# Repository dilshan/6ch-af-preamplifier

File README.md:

# 5.1 channel audio preamplifier

This project introduces a digitally controlled 5.1 channel audio preamplifier system. This amplifier is specifically designed to increase the gain of the multi-channel PC sound cards.

This preamplifier consists of six *[TL074](https://octopart.com/tl074idt-stmicroelectronics-410591)*/*[TL072](https://octopart.com/tl072idt-stmicroelectronics-410448)* preamplifier stages and *[PT2258](http://www.princeton.com.tw/Portals/0/Product/PT2258.pdf)* electronic volume control. The input stage of this preamplifier consists of six *TL074*/*TL072* buffer stages. The *[PIC16F886](https://www.microchip.com/en-us/product/PIC16F886)* microcontroller manages the *PT2258* electronic volume control IC. All the volume levels and menu options are displayed on [*HD44780*, 16×2 character LCD screen](https://s.click.aliexpress.com/e/_9iRz4T).

The provided PCB design contains a preamplifier, buffer stages, digital volume control circuit, driver circuit, and power supply unit.

The project was sponsored by *[PCBWay](https://www.pcbway.com/setinvite.aspx?inviteid=341430)*. The accurately configured PCB of this preamplifier can directly [order from *PCBWay*](https://www.pcbway.com/project/shareproject/5_1_channel_audio_preamplifier.html) through their website. The dimension of the PCB is 151.45 × 50.76mm.

This preamplifier is a [certified](https://certification.oshwa.org/lk000010.html) open hardware project. All source codes, *KiCAD* design files, and compiled binaries are available at this repository.

The complete [documentation](https://github.com/dilshan/6ch-af-preamplifier/wiki) of this project is available in the [wiki](https://github.com/dilshan/6ch-af-preamplifier/wiki) section of this repository. The PCB *Gerber files* and compiled binaries are also available in the [release](https://github.com/dilshan/6ch-af-preamplifier/releases) section of this repository.

All the content of this project are distributed under the terms of the following license:

- Hardware License: [CERN-OHL-W 2.0](https://ohwr.org/cern_ohl_w_v2.txt)
- Software License: [MIT](https://github.com/dilshan/6ch-af-preamplifier/blob/main/LICENSE)
- [Documentation](https://github.com/dilshan/6ch-af-preamplifier/wiki) License: [CC BY 4.0](https://creativecommons.org/licenses/by/4.0/)

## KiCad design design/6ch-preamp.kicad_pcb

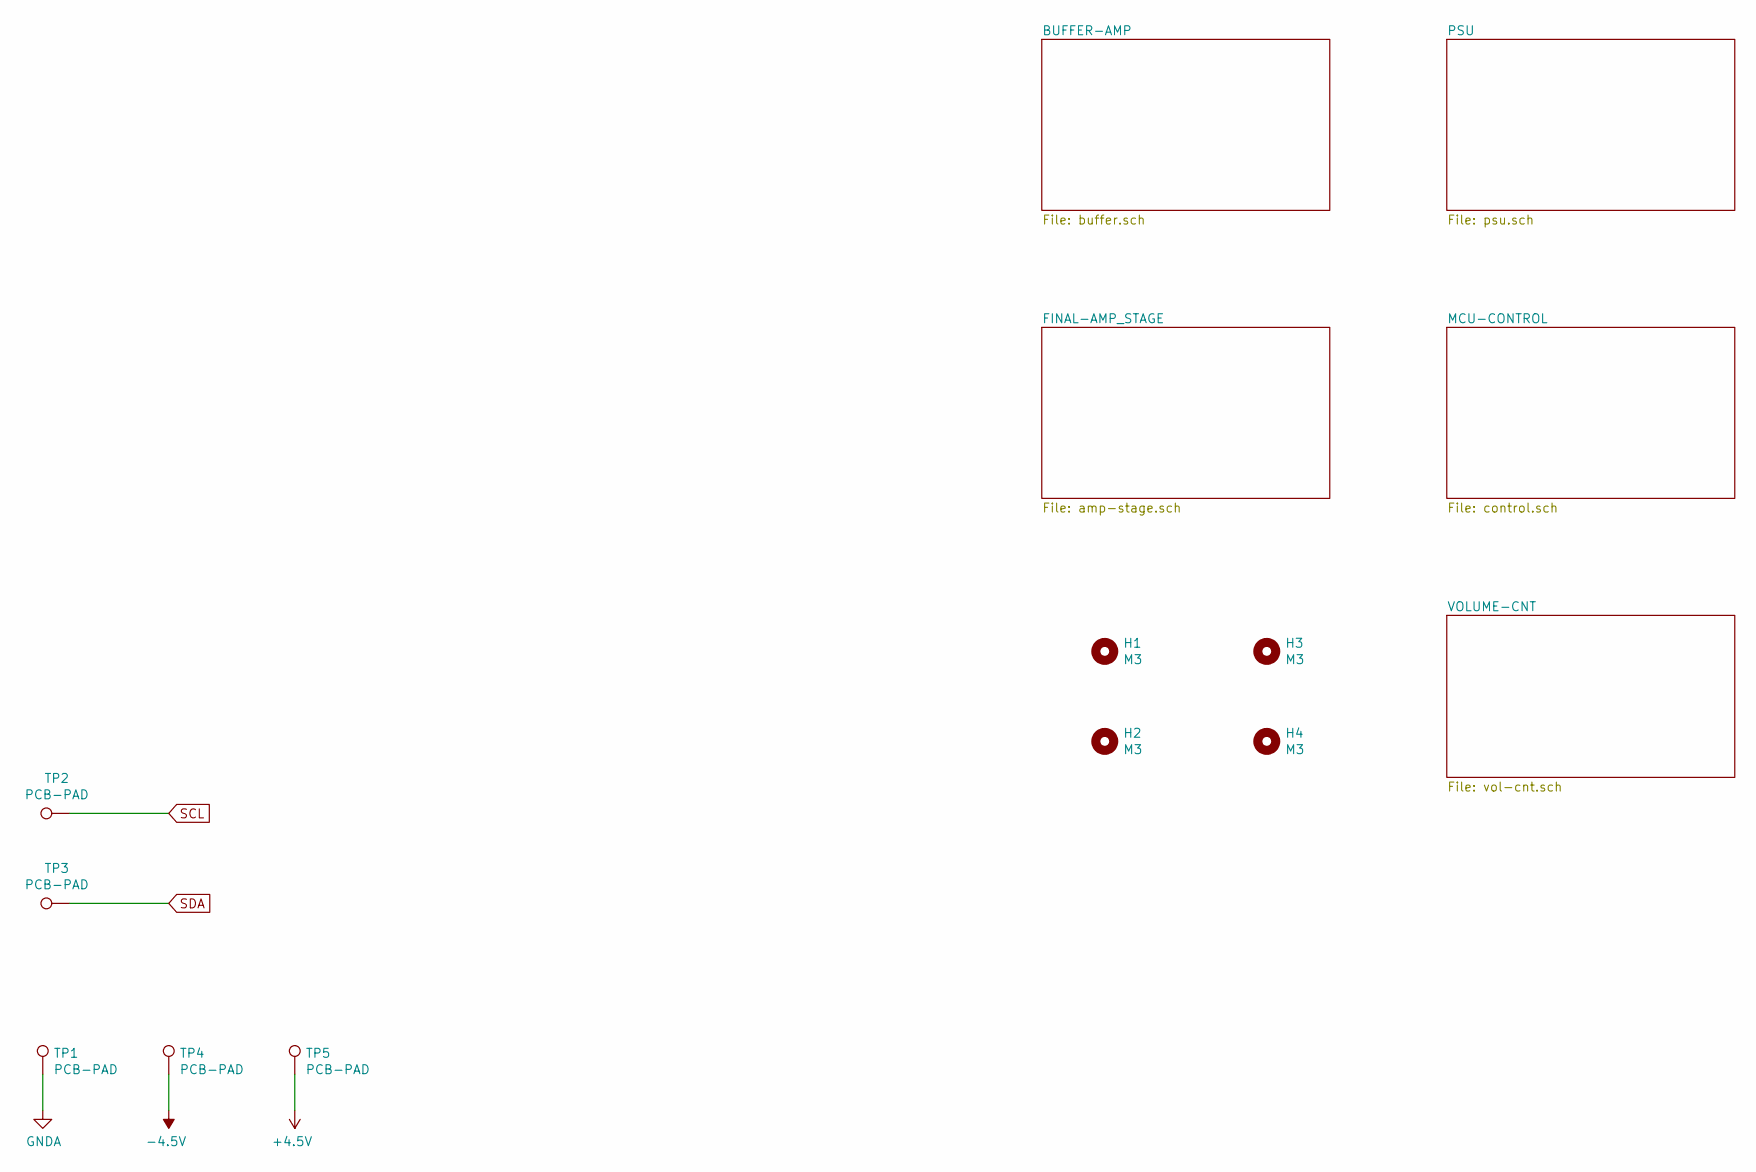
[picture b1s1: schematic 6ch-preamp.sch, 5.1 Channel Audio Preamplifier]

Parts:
H1, H2, H3, H4: M3; MountingHole_3.2mm_M3_DIN965_Pad
TP1, TP2, TP3, TP4, TP5: PCB-PAD; TestPoint_Pad_D2.0mm

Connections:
+1V35: TP5.1; also elsewhere on the board
-5V: TP4.1; also elsewhere on the board
GNDA: TP1.1; also elsewhere on the board
SCL: TP2.1; also elsewhere on the board
SDA: TP3.1; also elsewhere on the board

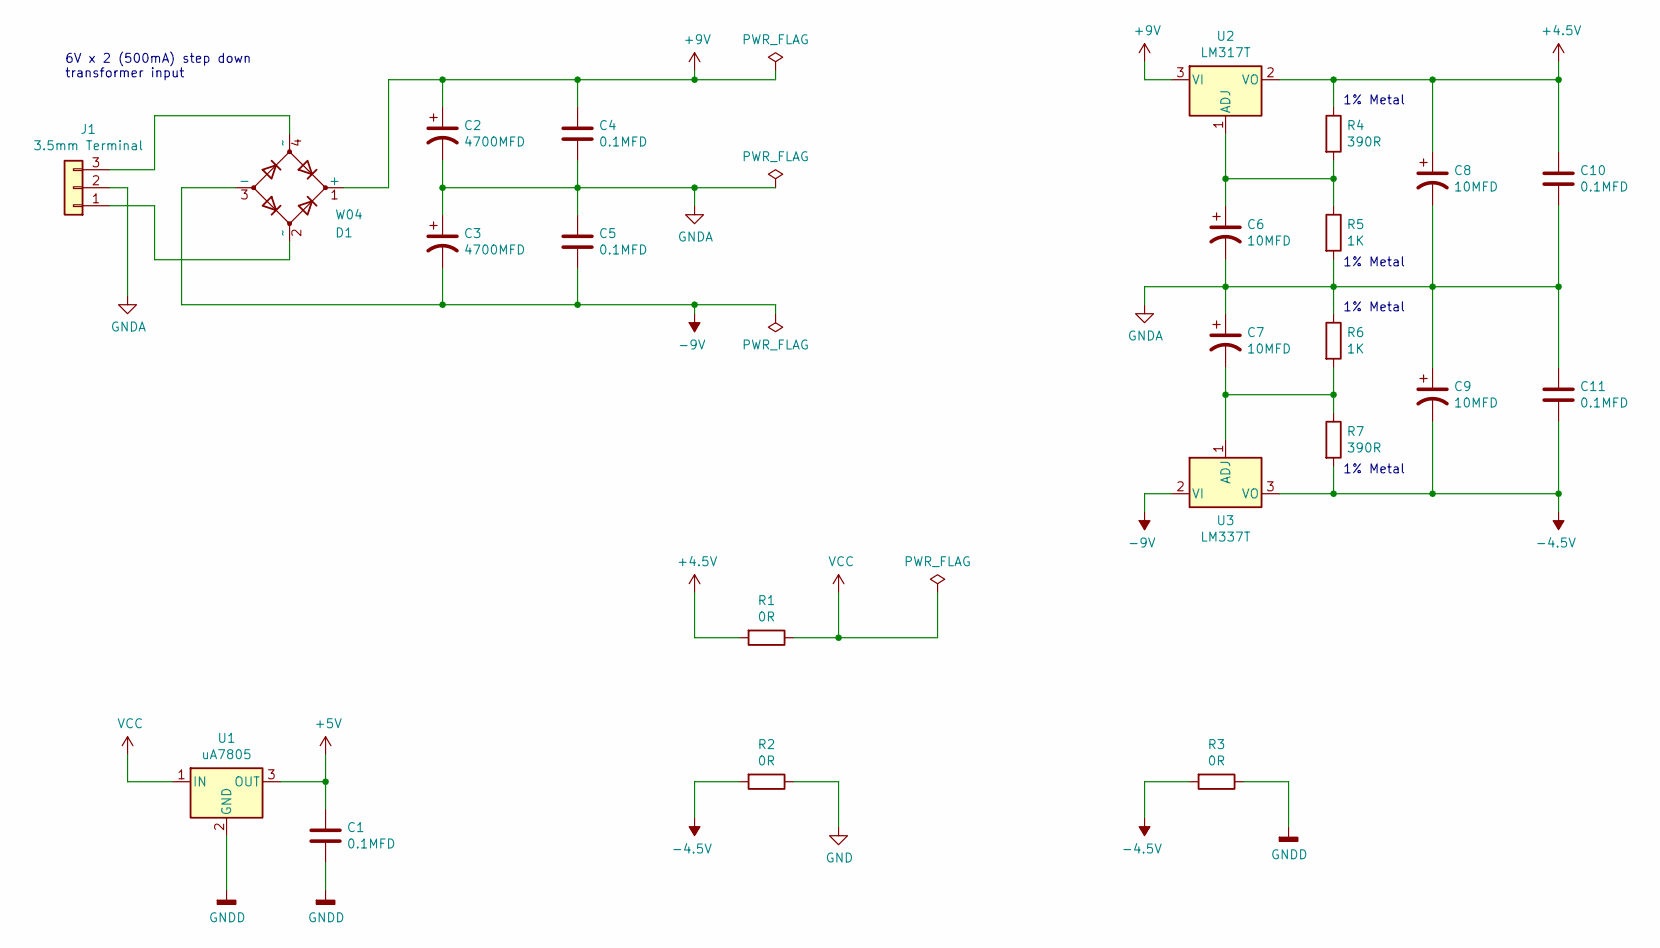
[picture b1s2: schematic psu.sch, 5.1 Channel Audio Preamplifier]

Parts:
C1, C10, C11: 0.1MFD; C_0805_2012Metric_Pad1.18x1.45mm_HandSolder
C2, C3: 4700MFD; CP_Radial_D30.0mm_P10.00mm_SnapIn
C4, C5: 0.1MFD; C_Disc_D10.5mm_W5.0mm_P10.00mm
C6, C7, C8, C9: 10MFD; CP_Elec_5x5.3
D1: W04; Diode_Bridge_Round_D9.0mm
J1: 3.5mm Terminal; PhoenixContact_MCV_1,5_3-G-3.5_1x03_P3.50mm_Vertical
R1, R2, R3: 0R; R_Axial_DIN0204_L3.6mm_D1.6mm_P2.54mm_Vertical
R4, R7: 390R; R_Axial_DIN0207_L6.3mm_D2.5mm_P10.16mm_Horizontal
R5, R6: 1K; R_Axial_DIN0207_L6.3mm_D2.5mm_P10.16mm_Horizontal
U1: uA7805; TO-220-3_Vertical
U2: LM317T; TO-220-3_Vertical
U3: LM337T; TO-220-3_Vertical

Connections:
+1V35: C8.1, C10.1, R1.2, R4.1, U2.2 (VO); also elsewhere on the board
+5V: C1.1, U1.3 (OUT); also elsewhere on the board
+9V: C2.1, C4.1, D1.1 (+), U2.3 (VI)
-5V: C9.2, C11.2, R2.2, R3.2, R7.2, U3.3 (VO); also elsewhere on the board
-9V: C3.2, C5.2, D1.3 (-), U3.2 (VI)
GND: R2.1; also elsewhere on the board
GNDA: C2.2, C3.1, C4.2, C5.1, C6.2, C7.1, C8.2, C9.1, C10.2, C11.1, J1.2, R5.2, R6.1; also elsewhere on the board
GNDD: C1.2, R3.1, U1.2 (GND); also elsewhere on the board
unnamed: C6.1, R4.2, R5.1, U2.1 (ADJ)
unnamed: C7.2, R6.2, R7.1, U3.1 (ADJ)
unnamed: D1.2 (~~), J1.1
unnamed: D1.4 (~~), J1.3
VCC: R1.1, U1.1 (IN); also elsewhere on the board

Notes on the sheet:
6V x 2 (500mA) step down transformer input
1% Metal

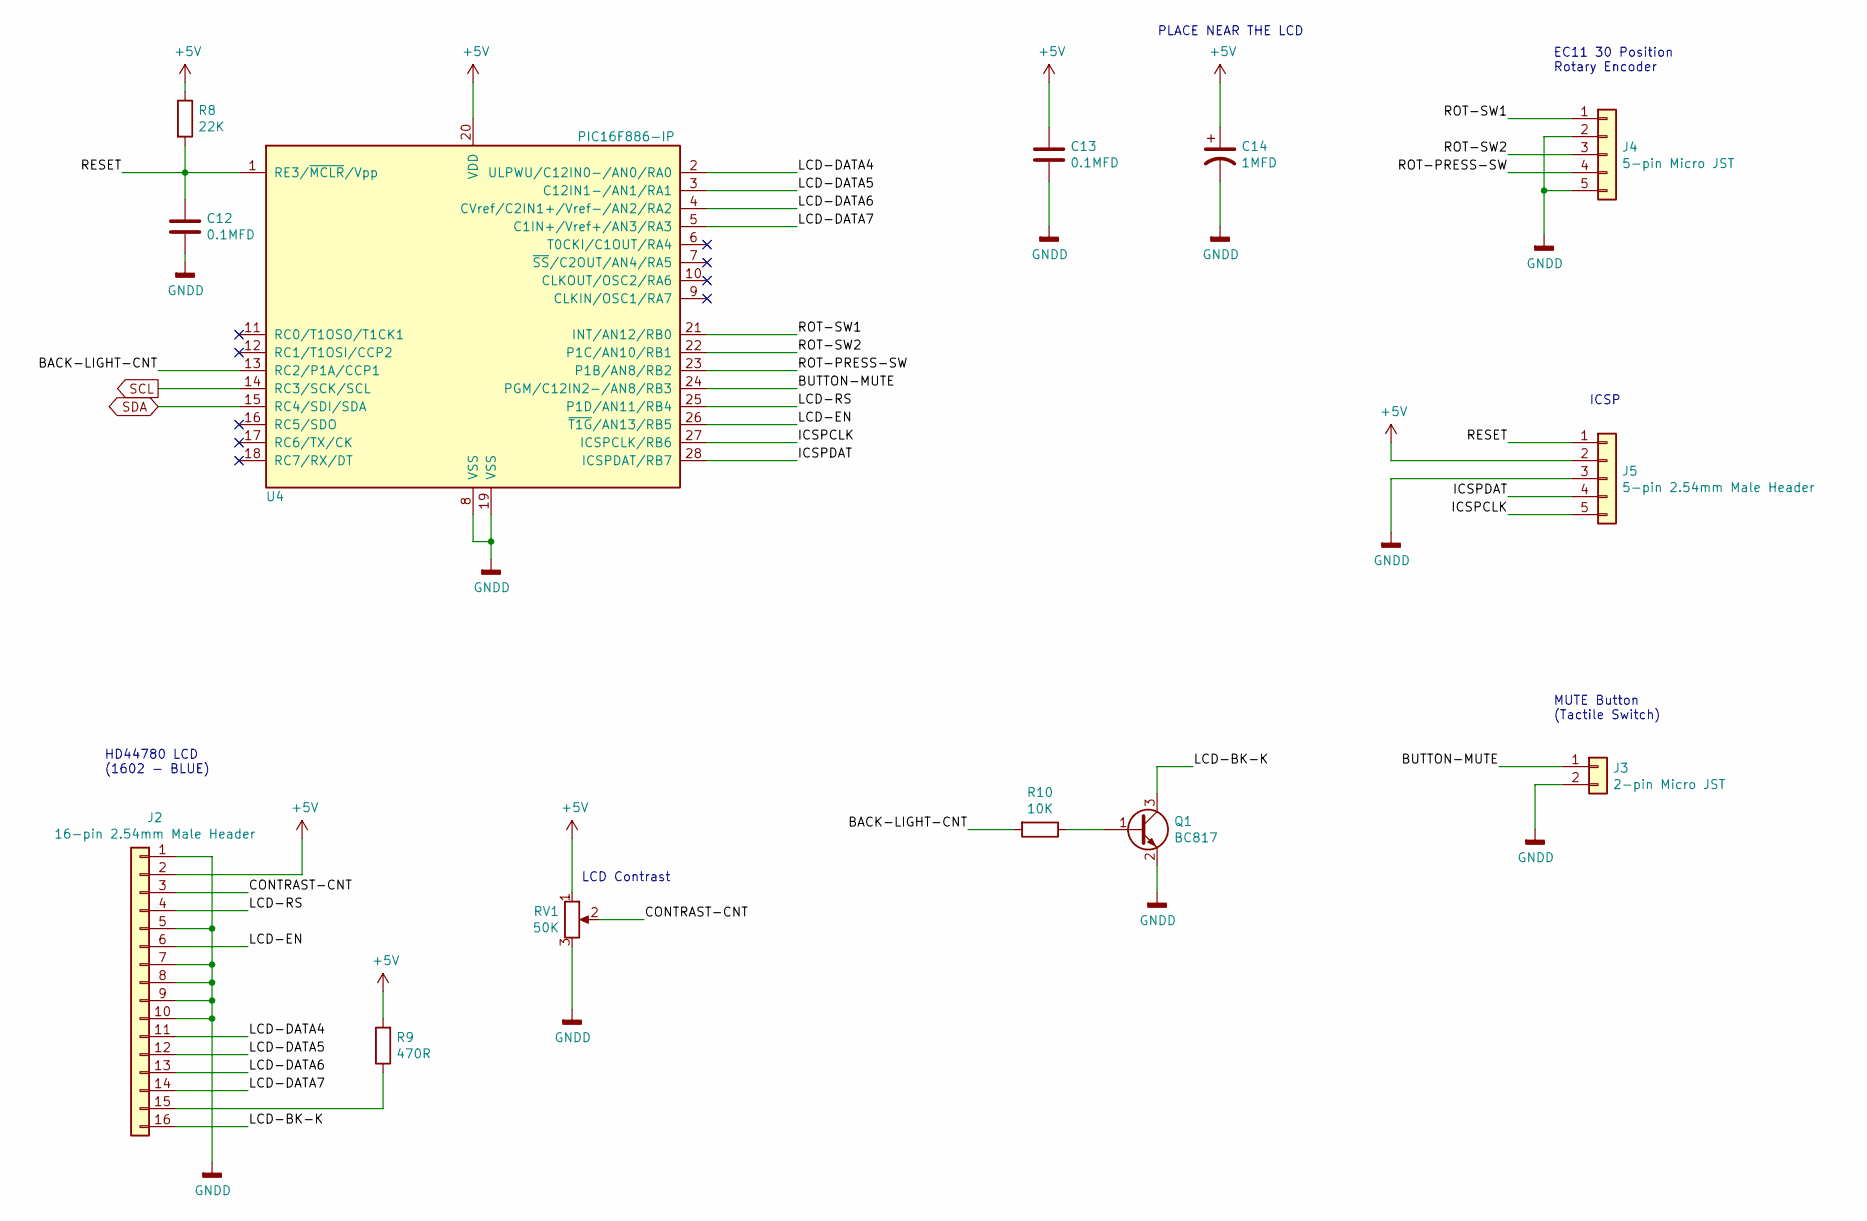
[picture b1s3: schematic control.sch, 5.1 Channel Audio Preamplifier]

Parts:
C12, C13: 0.1MFD; C_0805_2012Metric_Pad1.18x1.45mm_HandSolder
C14: 1MFD; CP_Elec_4x5.3
J2: 16-pin 2.54mm Male Header; PinHeader_1x16_P2.54mm_Vertical
J3: 2-pin Micro JST; JST_EH_B2B-EH-A_1x02_P2.50mm_Vertical
J4: 5-pin Micro JST; JST_EH_B5B-EH-A_1x05_P2.50mm_Vertical
J5: 5-pin 2.54mm Male Header; PinHeader_1x05_P2.54mm_Vertical
Q1: BC817; SOT-23
R8: 22K; R_0805_2012Metric_Pad1.20x1.40mm_HandSolder
R9: 470R; R_0805_2012Metric_Pad1.20x1.40mm_HandSolder
R10: 10K; R_0805_2012Metric_Pad1.20x1.40mm_HandSolder
RV1: 50K; Potentiometer_Bourns_TC33X_Vertical
U4: PIC16F886-IP; SSOP-28_5.3x10.2mm_P0.65mm

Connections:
+5V: C13.1, C14.1, J2.2, J5.2, R8.1, R9.2, RV1.1, U4.20 (VDD); also elsewhere on the board
/MCU-CONTROL/BACK-LIGHT-CNT: R10.2, U4.13 (RC2/P1A/CCP1)
/MCU-CONTROL/BUTTON-MUTE: J3.1, U4.24 (PGM/C12IN2-/AN8/RB3)
/MCU-CONTROL/CONTRAST-CNT: J2.3, RV1.2
/MCU-CONTROL/ICSPCLK: J5.5, U4.27 (ICSPCLK/RB6)
/MCU-CONTROL/ICSPDAT: J5.4, U4.28 (ICSPDAT/RB7)
/MCU-CONTROL/LCD-BK-K: J2.16, Q1.3 (C)
/MCU-CONTROL/LCD-DATA4: J2.11, U4.2 (ULPWU/C12IN0-/AN0/RA0)
/MCU-CONTROL/LCD-DATA5: J2.12, U4.3 (C12IN1-/AN1/RA1)
/MCU-CONTROL/LCD-DATA6: J2.13, U4.4 (CVref/C2IN1+/Vref-/AN2/RA2)
/MCU-CONTROL/LCD-DATA7: J2.14, U4.5 (C1IN+/Vref+/AN3/RA3)
/MCU-CONTROL/LCD-EN: J2.6, U4.26 (~T1G~/AN13/RB5)
/MCU-CONTROL/LCD-RS: J2.4, U4.25 (P1D/AN11/RB4)
/MCU-CONTROL/RESET: C12.1, J5.1, R8.2, U4.1 (RE3/~MCLR~/Vpp)
/MCU-CONTROL/ROT-PRESS-SW: J4.4, U4.23 (P1B/AN8/RB2)
/MCU-CONTROL/ROT-SW1: J4.1, U4.21 (INT/AN12/RB0)
/MCU-CONTROL/ROT-SW2: J4.3, U4.22 (P1C/AN10/RB1)
GNDD: C12.2, C13.2, C14.2, J2.1, J2.5, J2.7, J2.8, J2.9, J2.10, J3.2, J4.2, J4.5, J5.3, Q1.2 (E), RV1.3, U4.8 (VSS), U4.19 (VSS); also elsewhere on the board
unnamed: J2.15, R9.1
unnamed: Q1.1 (B), R10.1
SCL: U4.14 (RC3/SCK/SCL); also elsewhere on the board
SDA: U4.15 (RC4/SDI/SDA); also elsewhere on the board

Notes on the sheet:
EC11 30 Position Rotary Encoder
ICSP
MUTE Button (Tactile Switch)
HD44780 LCD (1602 - BLUE)
LCD Contrast
PLACE NEAR THE LCD

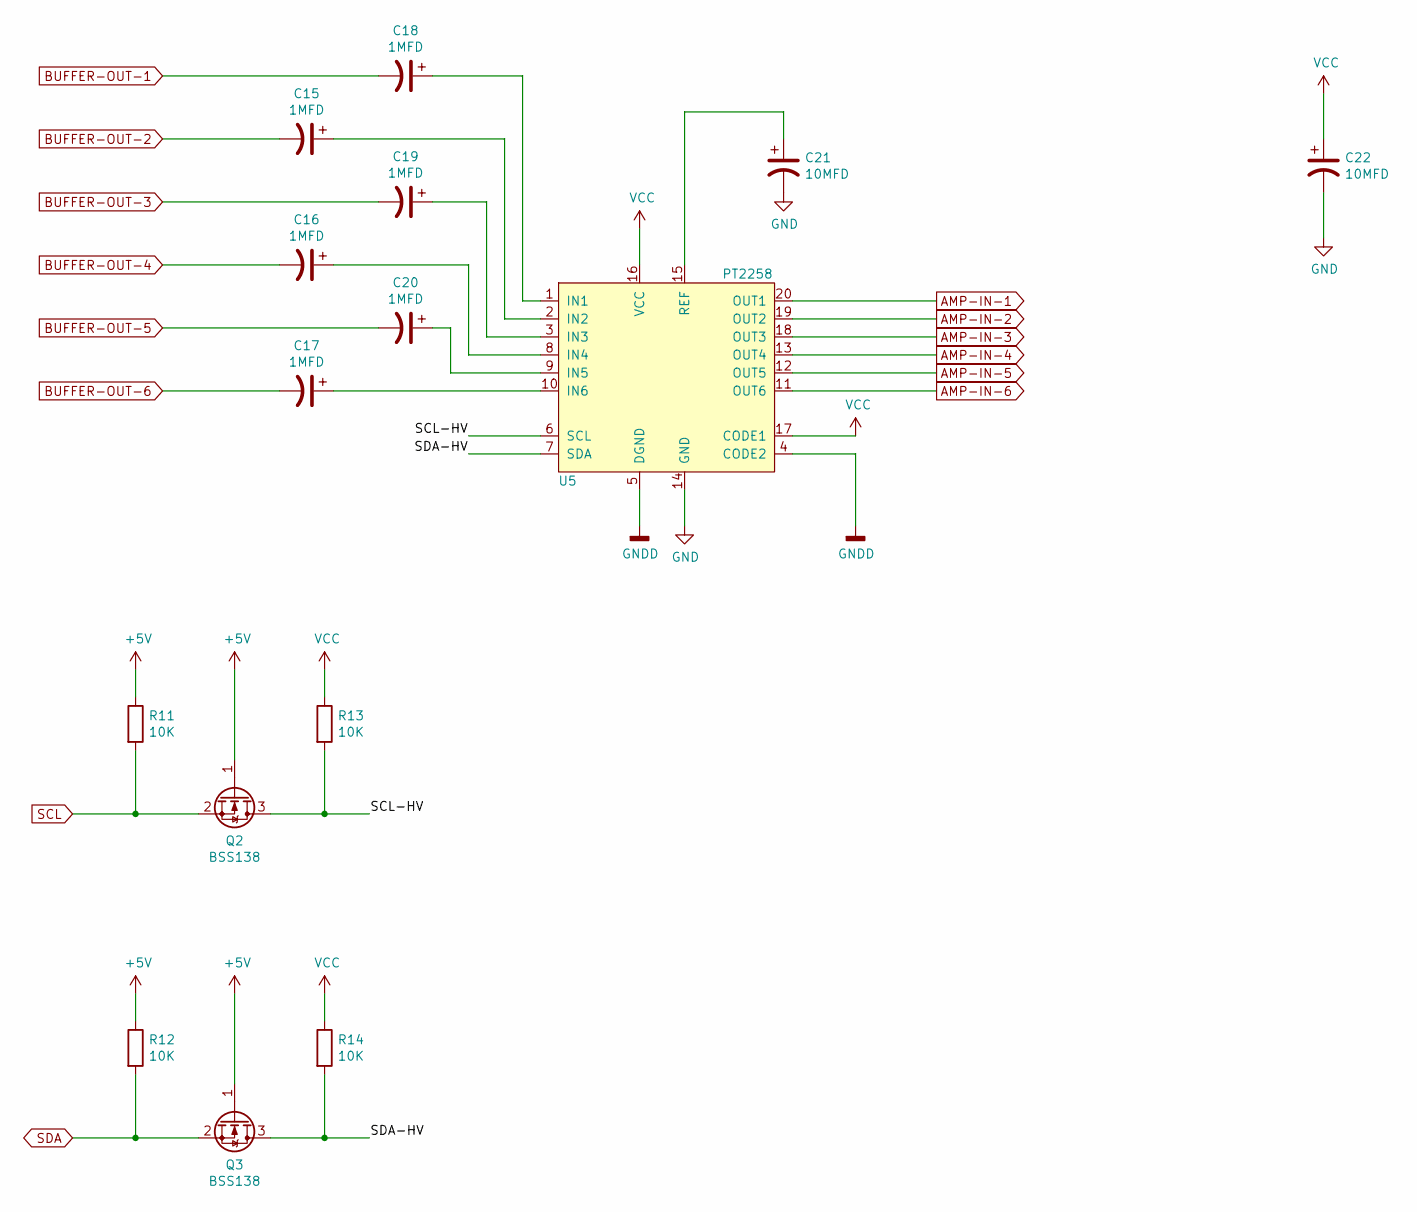
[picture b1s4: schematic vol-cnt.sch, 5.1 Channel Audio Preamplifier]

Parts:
C15, C16, C17, C18, C19, C20: 1MFD; CP_Elec_4x5.3
C21, C22: 10MFD; CP_Elec_5x5.3
Q2, Q3: BSS138; SOT-23
R11, R12, R13, R14: 10K; R_0805_2012Metric_Pad1.20x1.40mm_HandSolder
U5: PT2258; DIP-20_W7.62mm_LongPads

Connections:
+5V: Q2.1 (G), Q3.1 (G), R11.1, R12.1; also elsewhere on the board
/VOLUME-CNT/SCL-HV: Q2.3 (D), R13.2, U5.6 (SCL)
/VOLUME-CNT/SDA-HV: Q3.3 (D), R14.2, U5.7 (SDA)
AMP-IN-1: U5.20 (OUT1); also elsewhere on the board
AMP-IN-2: U5.19 (OUT2); also elsewhere on the board
AMP-IN-3: U5.18 (OUT3); also elsewhere on the board
AMP-IN-4: U5.13 (OUT4); also elsewhere on the board
AMP-IN-5: U5.12 (OUT5); also elsewhere on the board
AMP-IN-6: U5.11 (OUT6); also elsewhere on the board
BUFFER-OUT-1: C18.2; also elsewhere on the board
BUFFER-OUT-2: C15.2; also elsewhere on the board
BUFFER-OUT-3: C19.2; also elsewhere on the board
BUFFER-OUT-4: C16.2; also elsewhere on the board
BUFFER-OUT-5: C20.2; also elsewhere on the board
BUFFER-OUT-6: C17.2; also elsewhere on the board
GND: C21.2, C22.2, U5.14 (GND); also elsewhere on the board
GNDD: U5.4 (CODE2), U5.5 (DGND); also elsewhere on the board
unnamed: C15.1, U5.2 (IN2)
unnamed: C16.1, U5.8 (IN4)
unnamed: C17.1, U5.10 (IN6)
unnamed: C18.1, U5.1 (IN1)
unnamed: C19.1, U5.3 (IN3)
unnamed: C20.1, U5.9 (IN5)
unnamed: C21.1, U5.15 (REF)
SCL: Q2.2 (S), R11.2; also elsewhere on the board
SDA: Q3.2 (S), R12.2; also elsewhere on the board
VCC: C22.1, R13.1, R14.1, U5.16 (VCC), U5.17 (CODE1); also elsewhere on the board

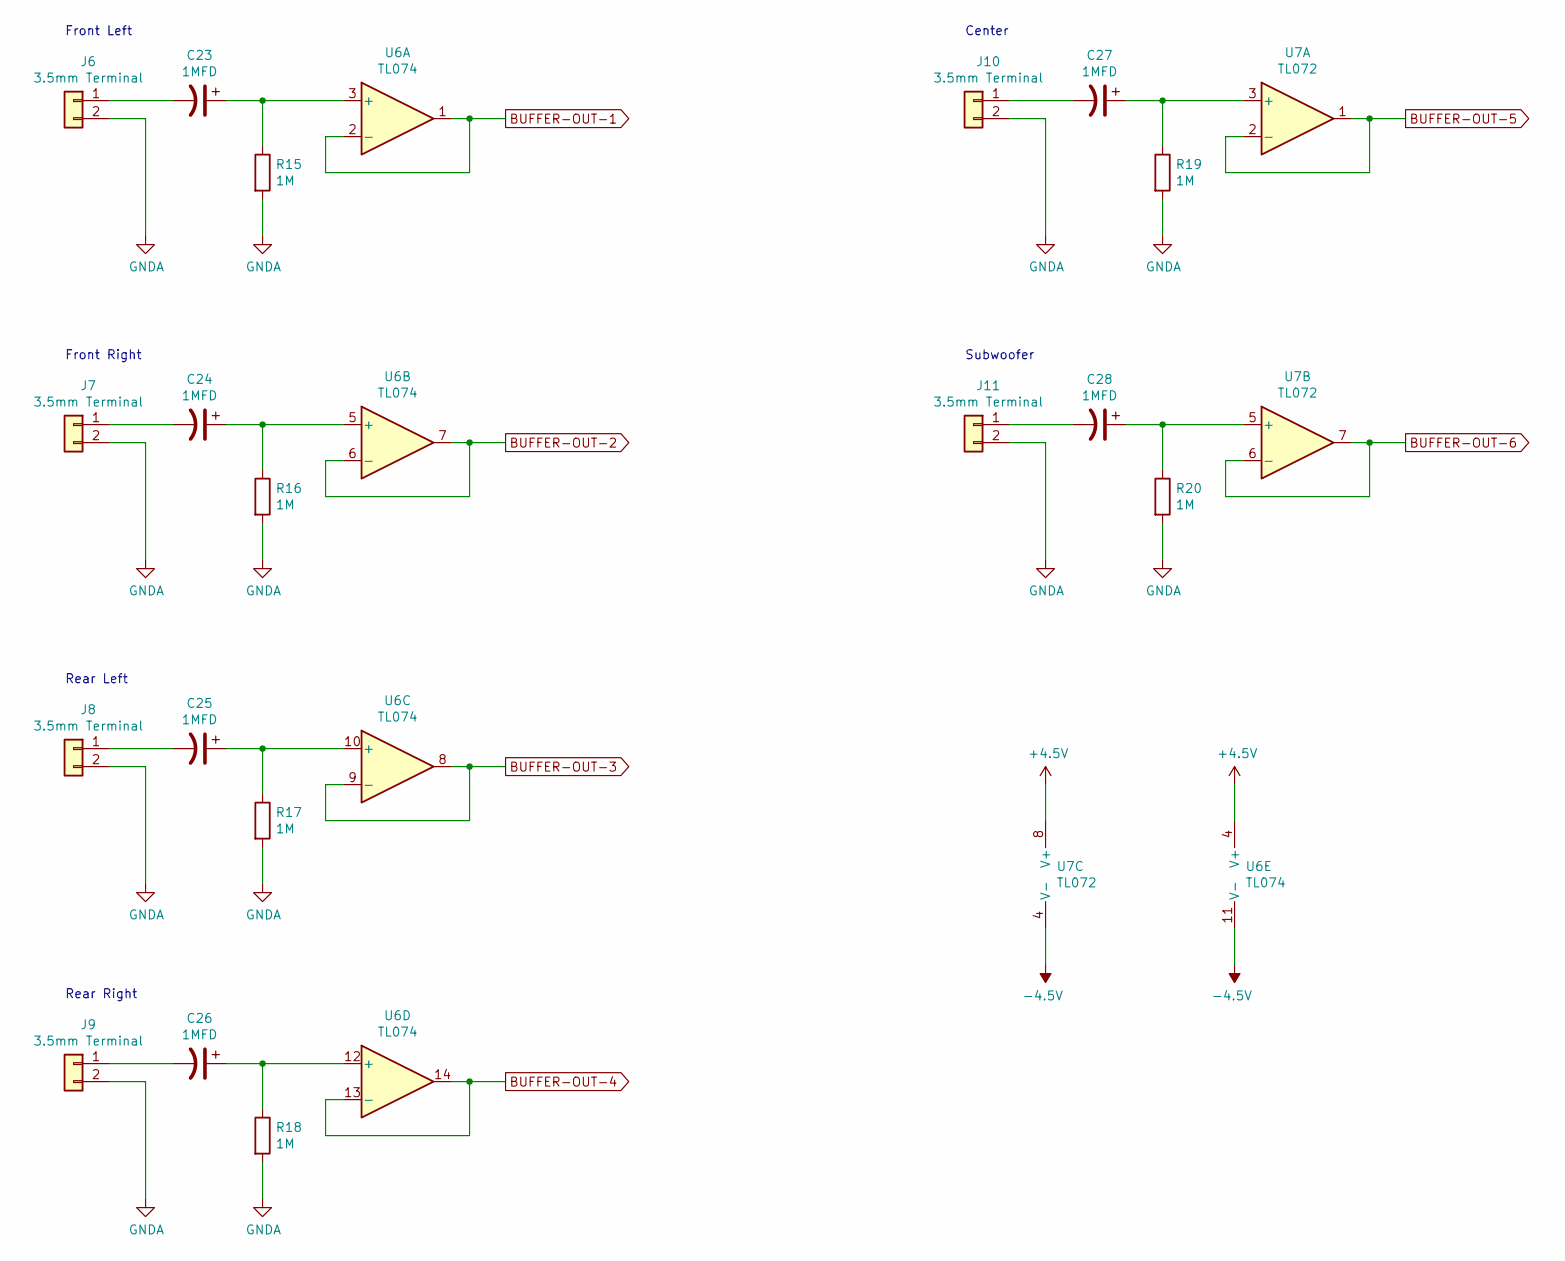
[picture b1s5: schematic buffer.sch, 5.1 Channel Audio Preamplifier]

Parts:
C23, C24, C25, C26, C27, C28: 1MFD; CP_Elec_4x5.3
J6, J7, J8, J9, J10, J11: 3.5mm Terminal; 3.50mm_PCB_Terminal
R15, R16, R17, R18, R19, R20: 1M; R_0805_2012Metric_Pad1.20x1.40mm_HandSolder
U6: TL074; SO-14_3.9x8.65mm_P1.27mm
U7: TL072; SO-8_3.9x4.9mm_P1.27mm

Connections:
+1V35: U6.4 (V+), U7.8 (V+); also elsewhere on the board
-5V: U6.11 (V-), U7.4 (V-); also elsewhere on the board
BUFFER-OUT-1: U6.1, U6.2 (-); also elsewhere on the board
BUFFER-OUT-2: U6.6 (-), U6.7; also elsewhere on the board
BUFFER-OUT-3: U6.8, U6.9 (-); also elsewhere on the board
BUFFER-OUT-4: U6.13 (-), U6.14; also elsewhere on the board
BUFFER-OUT-5: U7.1, U7.2 (-); also elsewhere on the board
BUFFER-OUT-6: U7.6 (-), U7.7; also elsewhere on the board
GNDA: J6.2, J7.2, J8.2, J9.2, J10.2, J11.2, R15.2, R16.2, R17.2, R18.2, R19.2, R20.2; also elsewhere on the board
unnamed: C23.1, R15.1, U6.3 (+)
unnamed: C23.2, J6.1
unnamed: C24.1, R16.1, U6.5 (+)
unnamed: C24.2, J7.1
unnamed: C25.1, R17.1, U6.10 (+)
unnamed: C25.2, J8.1
unnamed: C26.1, R18.1, U6.12 (+)
unnamed: C26.2, J9.1
unnamed: C27.1, R19.1, U7.3 (+)
unnamed: C27.2, J10.1
unnamed: C28.1, R20.1, U7.5 (+)
unnamed: C28.2, J11.1

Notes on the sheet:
Front Left
Front Right
Rear Left
Rear Right
Center
Subwoofer

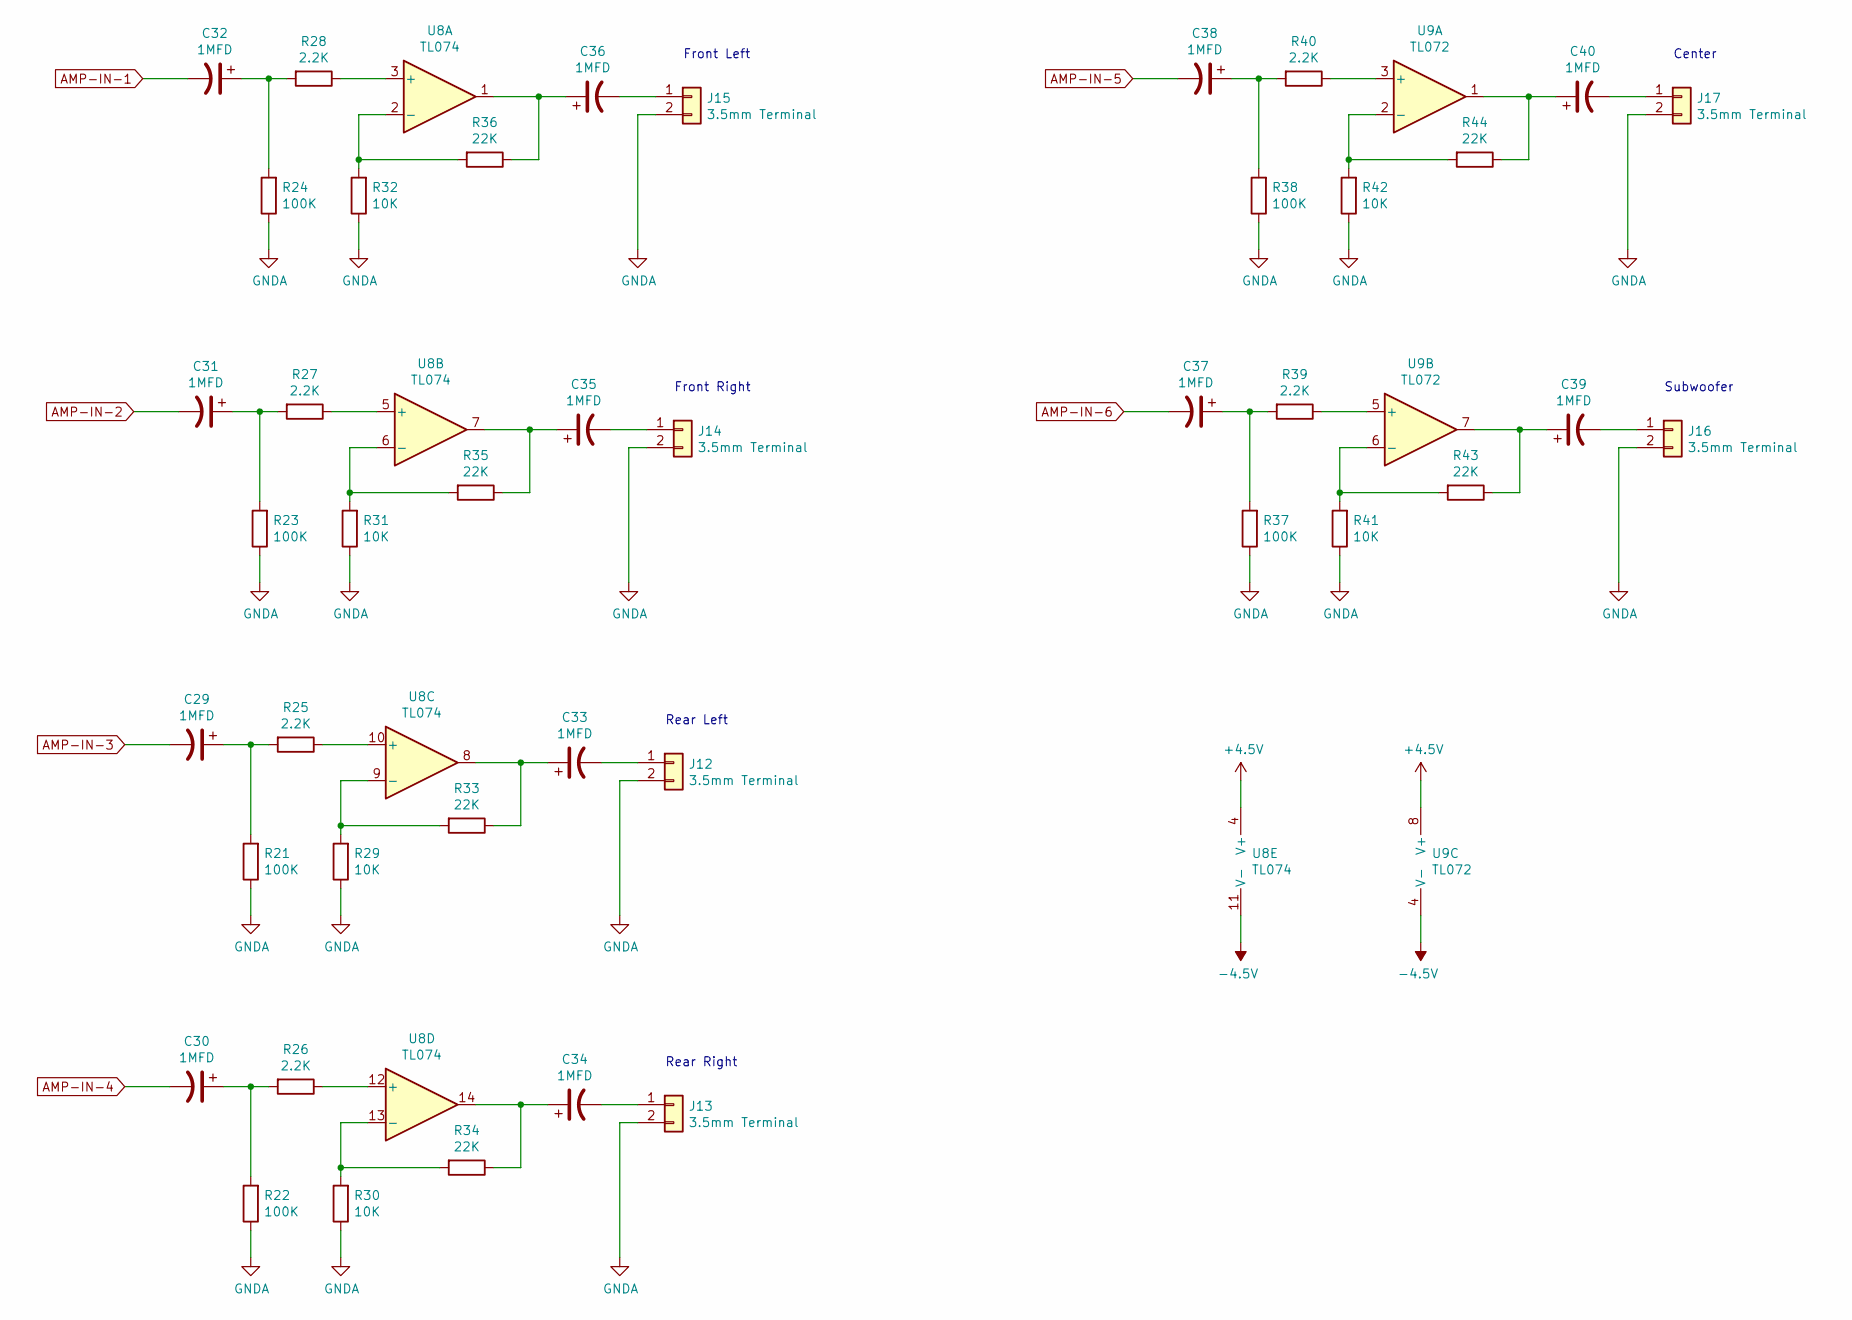
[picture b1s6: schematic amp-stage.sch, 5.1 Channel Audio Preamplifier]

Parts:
C29, C30, C31, C32, C33, C34, C35, C36, C37, C38, C39, C40: 1MFD; CP_Elec_4x5.3
J12, J13, J14, J15, J16, J17: 3.5mm Terminal; 3.50mm_PCB_Terminal
R21, R22, R23, R24, R37, R38: 100K; R_0805_2012Metric_Pad1.20x1.40mm_HandSolder
R25, R26, R27, R28, R39, R40: 2.2K; R_0805_2012Metric_Pad1.20x1.40mm_HandSolder
R29, R30, R31, R32, R41, R42: 10K; R_0805_2012Metric_Pad1.20x1.40mm_HandSolder
R33, R34, R35, R36, R43, R44: 22K; R_0805_2012Metric_Pad1.20x1.40mm_HandSolder
U8: TL074; SO-14_3.9x8.65mm_P1.27mm
U9: TL072; SO-8_3.9x4.9mm_P1.27mm

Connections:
+1V35: U8.4 (V+), U9.8 (V+); also elsewhere on the board
-5V: U8.11 (V-), U9.4 (V-); also elsewhere on the board
AMP-IN-1: C32.2; also elsewhere on the board
AMP-IN-2: C31.2; also elsewhere on the board
AMP-IN-3: C29.2; also elsewhere on the board
AMP-IN-4: C30.2; also elsewhere on the board
AMP-IN-5: C38.2; also elsewhere on the board
AMP-IN-6: C37.2; also elsewhere on the board
GNDA: J12.2, J13.2, J14.2, J15.2, J16.2, J17.2, R21.1, R22.1, R23.1, R24.1, R29.1, R30.1, R31.1, R32.1, R37.1, R38.1, R41.1, R42.1; also elsewhere on the board
unnamed: C29.1, R21.2, R25.2
unnamed: C30.1, R22.2, R26.2
unnamed: C31.1, R23.2, R27.2
unnamed: C32.1, R24.2, R28.2
unnamed: C33.1, R33.1, U8.8
unnamed: C33.2, J12.1
unnamed: C34.1, R34.1, U8.14
unnamed: C34.2, J13.1
unnamed: C35.1, R35.1, U8.7
unnamed: C35.2, J14.1
unnamed: C36.1, R36.1, U8.1
unnamed: C36.2, J15.1
unnamed: C37.1, R37.2, R39.2
unnamed: C38.1, R38.2, R40.2
unnamed: C39.1, R43.1, U9.7
unnamed: C39.2, J16.1
unnamed: C40.1, R44.1, U9.1
unnamed: C40.2, J17.1
unnamed: R25.1, U8.10 (+)
unnamed: R26.1, U8.12 (+)
unnamed: R27.1, U8.5 (+)
unnamed: R28.1, U8.3 (+)
unnamed: R29.2, R33.2, U8.9 (-)
unnamed: R30.2, R34.2, U8.13 (-)
unnamed: R31.2, R35.2, U8.6 (-)
unnamed: R32.2, R36.2, U8.2 (-)
unnamed: R39.1, U9.5 (+)
unnamed: R40.1, U9.3 (+)
unnamed: R41.2, R43.2, U9.6 (-)
unnamed: R42.2, R44.2, U9.2 (-)

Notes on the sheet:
Front Left
Front Right
Rear Left
Rear Right
Center
Subwoofer

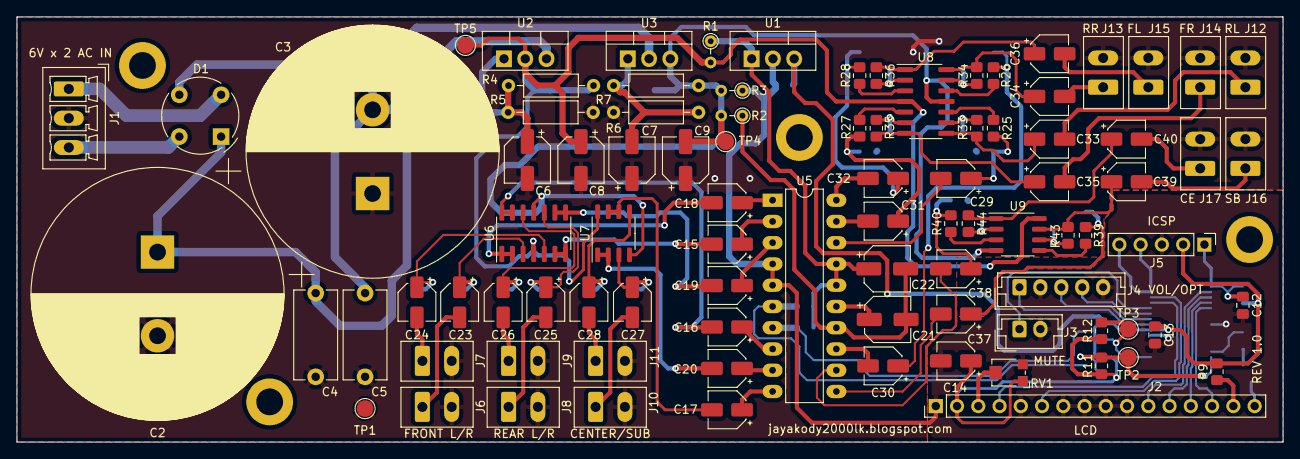
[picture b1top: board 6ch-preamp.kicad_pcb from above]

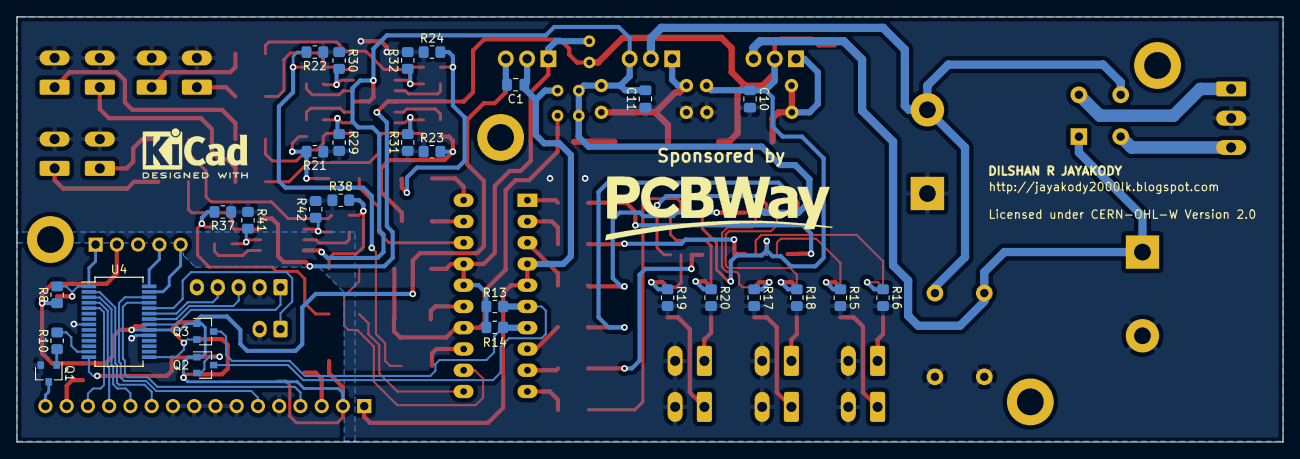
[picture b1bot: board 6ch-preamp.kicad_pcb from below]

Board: 2 copper layers, 151.3 x 50.8 mm, 124 parts (29 on the bottom side), 96 nets.

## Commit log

2021-10-26 Add initial version of KiCAD design files and heatsink design.
2021-10-26 Update KiCAD design files with GitHub repository link.
2021-10-26 Add initial version of README.md file.
2021-10-30 Update README.MD file with external web links.
2021-10-30 Add initial version of PIC16F886 firmware.
2021-10-30 Add build system information into the compiler.md file.
2021-11-01 Add initial version of wiring diagram project.
2021-11-01 Add YouTube preview image.
2021-11-01 Add YouTube video link to the README.MD file.
2021-11-04 Add OSHWA certification details.
2021-11-05 Add small version of LK000010 OSHWA certification logo.
2021-11-05 Update README.MD with certification details.

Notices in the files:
design/6ch-preamp.kicad_pcb:
Licensed under CERN-OHL-W Version 2.0
